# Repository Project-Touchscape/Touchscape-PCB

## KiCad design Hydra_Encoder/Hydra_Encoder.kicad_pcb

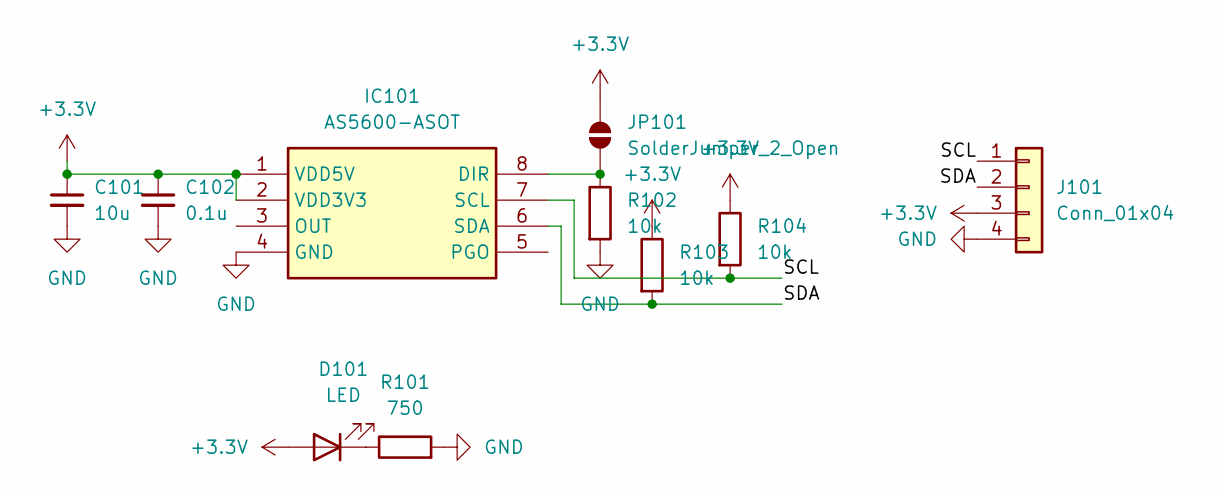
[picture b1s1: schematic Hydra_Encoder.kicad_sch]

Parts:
C101: 10u; C_0805_2012Metric
C102: 0.1u; C_0402_1005Metric
D101: LED; LED_0603_1608Metric
IC101: AS5600-ASOT; SOIC-8_3.9x4.9mm_P1.27mm; Manufacturer_Part_Number AS5600-ASOT; Mouser Part Number 985-AS5600-ASOT
J101: Conn_01x04; CONN_CCSH-W10R-04TR-BK-A_ADA
JP101: SolderJumper_2_Open; SolderJumper-2_P1.3mm_Open_RoundedPad1.0x1.5mm
R101: 750; R_0402_1005Metric
R102, R103, R104: 10k; R_0402_1005Metric

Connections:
+3.3V: C101.1, C102.1, D101.2 (A), IC101.1 (VDD5V), IC101.2 (VDD3V3), J101.3, JP101.2 (B), R103.1, R104.1
/SCL: IC101.7 (SCL), J101.1, R104.2
/SDA: IC101.6 (SDA), J101.2, R103.2
GND: C101.2, C102.2, IC101.4 (GND), J101.4, R101.2, R102.2
unnamed: D101.1 (K), R101.1
unnamed: IC101.8 (DIR), JP101.1 (A), R102.1

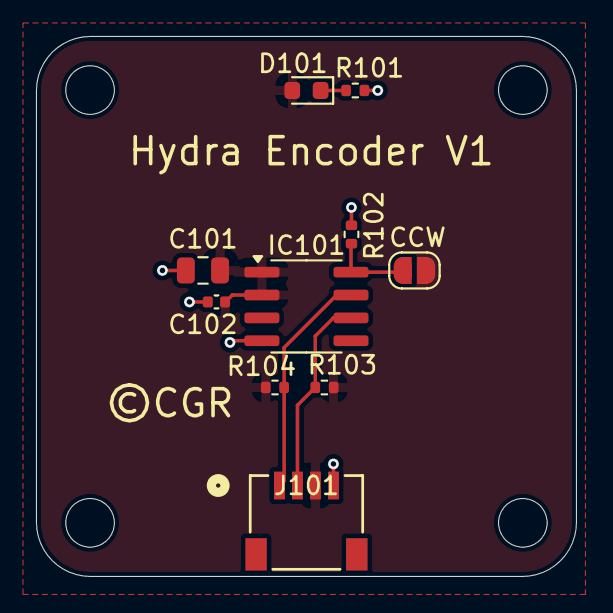
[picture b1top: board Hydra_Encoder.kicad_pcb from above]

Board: 2 copper layers, 30.0 x 30.0 mm, 10 parts (0 on the bottom side), 6 nets.

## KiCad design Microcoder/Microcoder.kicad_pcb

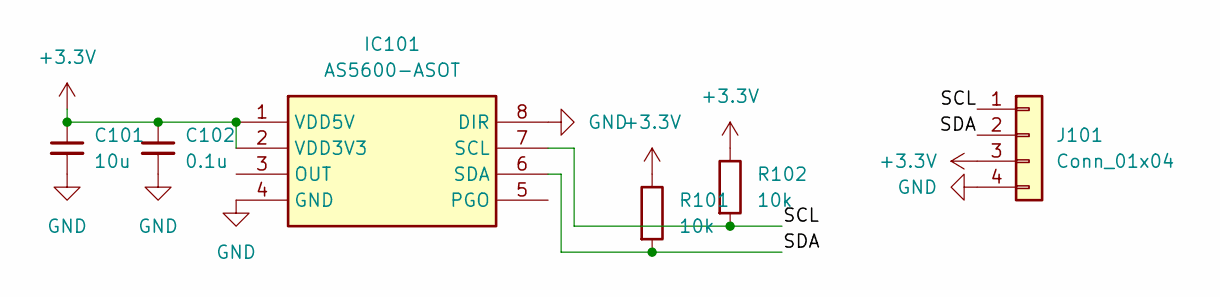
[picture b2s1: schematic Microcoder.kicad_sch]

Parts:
C101: 10u; C_0805_2012Metric
C102: 0.1u; C_0402_1005Metric
IC101: AS5600-ASOT; SOIC-8_3.9x4.9mm_P1.27mm; Manufacturer_Part_Number AS5600-ASOT; Mouser Part Number 985-AS5600-ASOT
J101: Conn_01x04; CONN_CCSH-W10R-04TR-BK-A_ADA
R101, R102: 10k; R_0402_1005Metric

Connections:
+3.3V: C101.1, C102.1, IC101.1 (VDD5V), IC101.2 (VDD3V3), J101.3, R101.1, R102.1
/SCL: IC101.7 (SCL), J101.1, R102.2
/SDA: IC101.6 (SDA), J101.2, R101.2
GND: C101.2, C102.2, IC101.4 (GND), IC101.8 (DIR), J101.4

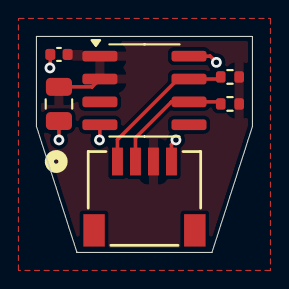
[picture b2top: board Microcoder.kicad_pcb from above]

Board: 2 copper layers, 12.0 x 12.0 mm, 6 parts (0 on the bottom side), 4 nets.

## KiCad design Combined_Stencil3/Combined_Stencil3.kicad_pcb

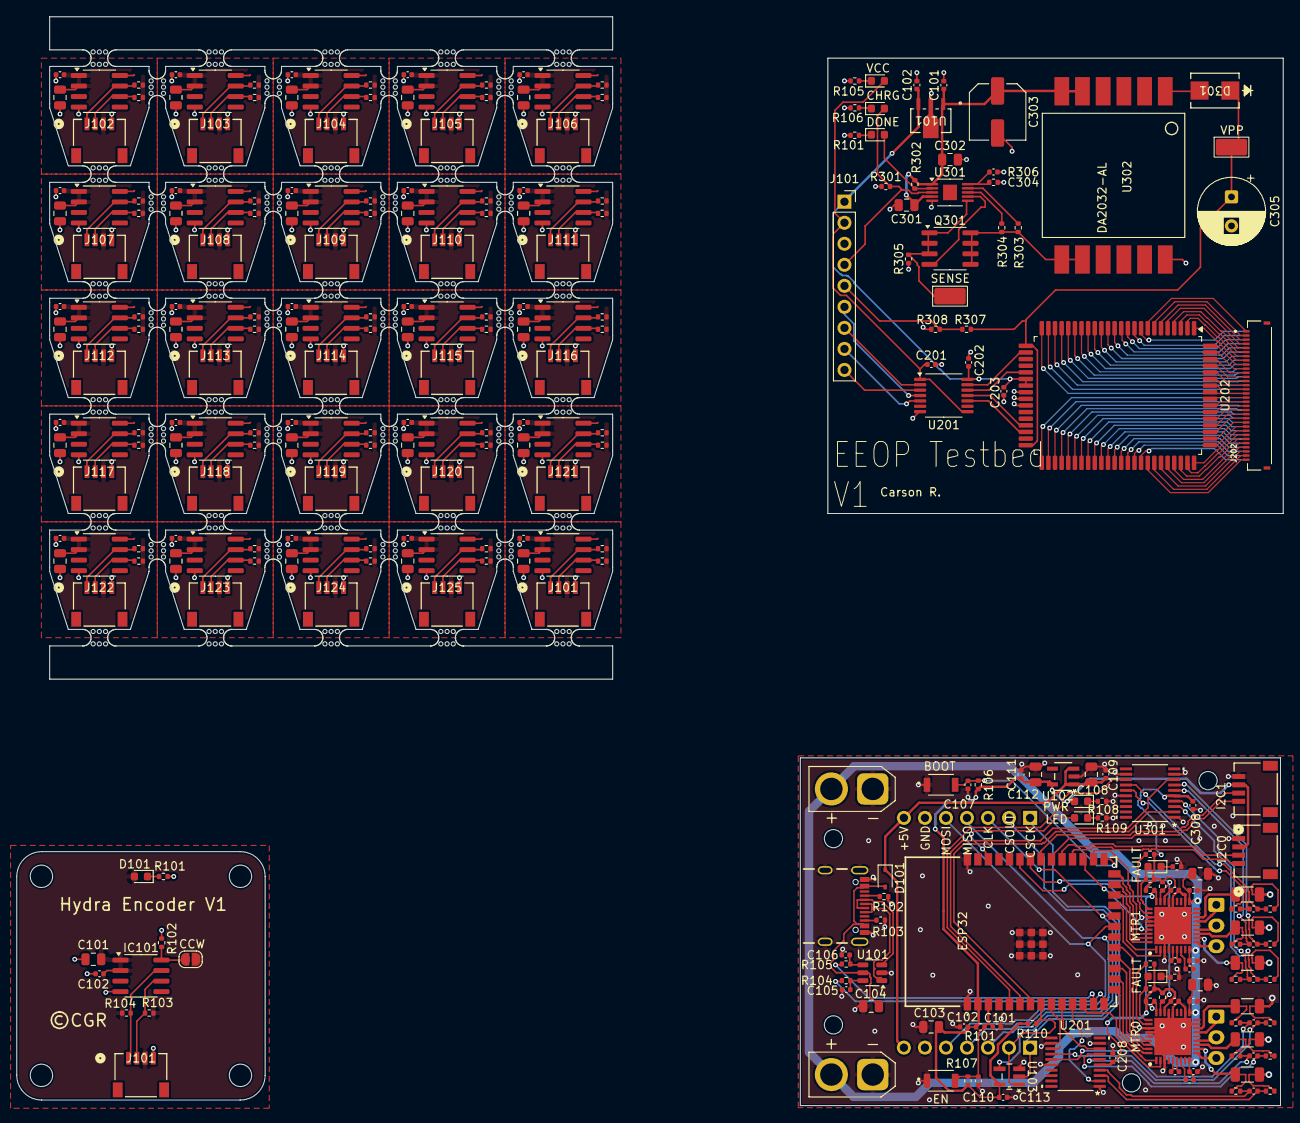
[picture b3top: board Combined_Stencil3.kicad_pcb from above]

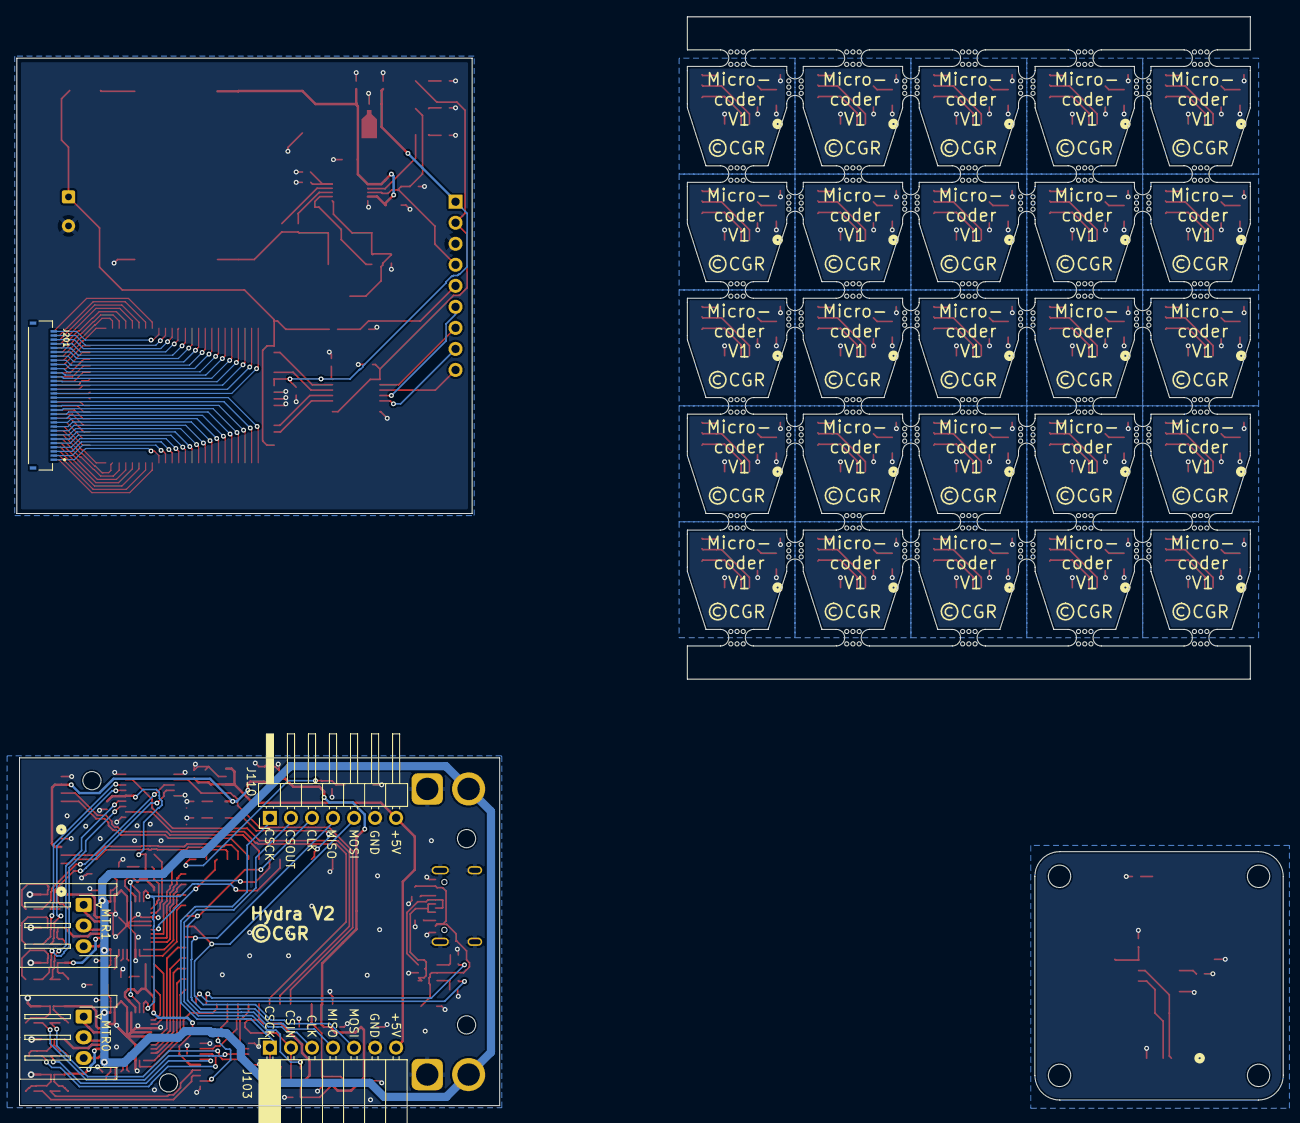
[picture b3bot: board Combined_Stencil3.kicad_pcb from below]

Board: 2 copper layers, 153.0 x 131.5 mm, 341 parts (5 on the bottom side), 174 nets.

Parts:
C101, C101#2, C103, C103#2, C104, C105#2, C107, C108, C109#2, C111#2, C112, C113, C115, C117, C119, C121, C123, C125, C127, C129, C131, C133, C135, C137, C139, C141, C143, C145, C147, C149, C206, C301, C302#2, C306: 10u; C_0805_2012Metric
C101#3, C101#4, C102, C102#2, C102#3, C102#4, C104#2, C106, C107#2, C108#2, C109, C110, C110#2, C111, C112#2, C113#2, C114, C116, C118, C120, C122, C124, C126, C128, C130, C132, C134, C136, C138, C140, C142, C144, C146, C148, C150, C201#2, C202, C202#2, C203#2, C207, C208, C209, C302, C307, C308, C309: 0.1u; C_0402_1005Metric
C105, C106#2, C304#2: 20p; C_0402_1005Metric
C201, C301#2: 0.01u; C_0402_1005Metric
C203, C204, C205, C303, C304, C305: 22n; C_0402_1005Metric
C210, C310: 0.47u; C_0402_1005Metric
C303#2: 56u; C_Elec_6.3x5.8
C305#2: 4.7u; CP_Radial_D8.0mm_P3.50mm
D101, D101#3, D102, D102#2, D103, D103#2, D201, D301#2: LED; LED_0603_1608Metric
D101#2: BAT60A; D_SOD-323
D301: D; SMB_DIO
IC101, IC101#3, IC102, IC103, IC104, IC105, IC106, IC107, IC108, IC109, IC110, IC111, IC112, IC113, IC114, IC115, IC116, IC117, IC118, IC119, IC120, IC121, IC122, IC123, IC124, IC125: AS5600-ASOT; SOIC-8_3.9x4.9mm_P1.27mm
IC101#2: ESP32-S3-WROOM-1-N4; ESP32S3WROOM1N4
IC201, IC301: DRV8313RHHR; QFN50P600X600X100-37N-D
J101, J101#2, J102#2, J103, J104, J104#2, J105, J106, J107, J107#2, J108, J109#2, J110, J111, J112, J113, J114, J115, J116, J117, J118, J119, J120, J121, J122, J123, J124, J125: Conn_01x04; CONN_CCSH-W10R-04TR-BK-A_ADA
J101#3: Conn_01x09; PinSocket_1x09_P2.54mm_Vertical
J101#4: USB4105-GF-A; GCT_USB4105-GF-A
J102, J109: Conn_01x02; AMASS_XT30U-F_1x02_P5.0mm_Vertical
J103#2: Conn_01x07; PinSocket_1x07_P2.54mm_Horizontal
J105#2, J108#2: Conn_01x03; JST_XH_S3B-XH-A-1_1x03_P2.50mm_Horizontal
J110#2: Conn_01x07; PinHeader_1x07_P2.54mm_Horizontal
J201, J202: Conn_01x32; HRS_FH34SRJ-32S-0.5SH_50_
JP101: SolderJumper_2_Open; SolderJumper-2_P1.3mm_Open_RoundedPad1.0x1.5mm
Q301: MCQ15N10YA; SOIC-8_3.9x4.9mm_P1.27mm
R101, R101#4, R102#2, R102#3, R103#2, R104, R104#3, R105, R106, R107, R107#2, R108, R110, R110#2, R111, R113, R114, R116, R117, R119, R120, R122, R123, R125, R126, R128, R129, R131, R132, R134, R135, R137, R138, R140, R141, R143, R144, R146, R147, R149, R150, R152, R153, R155, R156, R158, R159, R161, R162, R164, R165, R167, R168, R170, R171, R173, R174, R207, R208, R209, R210, R301, R307, R308, R309, R310: 10k; R_0402_1005Metric
R101#2: 750; R_0402_1005Metric
R101#3, R105#2, R106#2, R108#2, R109, R211, R311: 500; R_0402_1005Metric
R102, R103: 5.1kΩ; R_0402_1005Metric
R104#2, R105#3: 22Ω; R_0402_1005Metric
R201, R202, R203, R204, R205, R206, R301#2, R302#2, R303, R304#2, R305#2, R306: 10; R_0402_1005Metric
R212, R213, R214, R312, R313, R314: 25m; R_1206_3216Metric
R302: 100k; R_0402_1005Metric
R303#2: 60.4k; R_0402_1005Metric
R304: 43k; R_0402_1005Metric
R305: 13; R_0402_1005Metric
R306#2: 2.49k; R_0402_1005Metric
R307#2: 30M; R_0402_1005Metric
R308#2: 300k; R_0402_1005Metric
SW101, SW102: SW_SPST; SW_B3U-1000P
TP101, TP302: TestPoint; TestPoint_Keystone_5019_Miniature
U101: AS78L05RTR-E1; SOT-89_3MC_MCH
U101#2: USBLC6-2SC6; SOT-23-6
U102: MIC5504-3.3YM5-TR; SOT-23-5_MC_MCH
U103: SN74LVC1G80DBVR; DBV5
U201: TXB0104PW; TSSOP-14_4.4x5mm_P0.65mm
U201#2, U301: INA4181A3IPWR; PW20_TEX
U202: HV507PG-G; PQFP-80_14x20mm_P0.8mm
U301#2: LT3750AEMS-TRPBF; MSOP-10-1EP_3x3mm_P0.5mm_EP1.68x1.88mm
U302: DA2032-AL
mouse-bite-2mm-slot, mouse-bite-2mm-slot1, mouse-bite-2mm-slot3, mouse-bite-2mm-slot4, mouse-bite-2mm-slot5, mouse-bite-2mm-slot6, mouse-bite-2mm-slot7, mouse-bite-2mm-slot8, mouse-bite-2mm-slot9, mouse-bite-2mm-slot10, mouse-bite-2mm-slot11, mouse-bite-2mm-slot13, mouse-bite-2mm-slot14, mouse-bite-2mm-slot15, mouse-bite-2mm-slot16, mouse-bite-2mm-slot17, mouse-bite-2mm-slot18, mouse-bite-2mm-slot19, mouse-bite-2mm-slot20, mouse-bite-2mm-slot21, mouse-bite-2mm-slot23, mouse-bite-2mm-slot24, mouse-bite-2mm-slot25, mouse-bite-2mm-slot26, mouse-bite-2mm-slot27, mouse-bite-2mm-slot28, mouse-bite-2mm-slot29, mouse-bite-2mm-slot30, mouse-bite-2mm-slot31, mouse-bite-2mm-slot33, mouse-bite-2mm-slot34, mouse-bite-2mm-slot35, mouse-bite-2mm-slot36, mouse-bite-2mm-slot37, mouse-bite-2mm-slot38, mouse-bite-2mm-slot39, mouse-bite-2mm-slot40, mouse-bite-2mm-slot41, mouse-bite-2mm-slot41#2, mouse-bite-2mm-slot43, mouse-bite-2mm-slot43#2, mouse-bite-2mm-slot44, mouse-bite-2mm-slot45, mouse-bite-2mm-slot45#2, mouse-bite-2mm-slot46, mouse-bite-2mm-slot47, mouse-bite-2mm-slot47#2, mouse-bite-2mm-slot48, mouse-bite-2mm-slot#2, mouse-bite-2mm-slot#3: VAL**; mouse-bite-2mm-slot

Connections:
+3.3V: C101.1, C101#2.1, C102.2, C102#3.1, C102#4.1, C103.2, C103#2.1, C104#2.1, C105#2.1, C106.1, C107.1, C108#2.1, C109#2.1, C110#2.1, C111.1, C111#2.1, C112.1, C112#2.1, C113.1, C113#2.1, C114.1, C115.1, C116.1, C117.1, C118.1, C119.1, C120.1, C121.1, C122.1, C123.1, C124.1, C125.1, C126.1, C127.1, C128.1, C129.1, C130.1, C131.1, C132.1, C133.1, C134.1, C135.1, C136.1, C137.1, C138.1, C139.1, C140.1, C141.1, C142.1, C143.1, C144.1, C145.1, C146.1, C147.1, C148.1, C149.1, C150.1, C201#2.2, D101.2 (A), D101#3.2 (A), D102.2 (A), IC101.1 (VDD5V), IC101.2 (VDD3V3), IC101#2.2 (3V3), IC101#3.1 (VDD5V), IC101#3.2 (VDD3V3), IC102.1 (VDD5V), IC102.2 (VDD3V3), IC103.1 (VDD5V), IC103.2 (VDD3V3), IC104.1 (VDD5V), IC104.2 (VDD3V3), IC105.1 (VDD5V), IC105.2 (VDD3V3), IC106.1 (VDD5V), IC106.2 (VDD3V3), IC107.1 (VDD5V), IC107.2 (VDD3V3), IC108.1 (VDD5V), IC108.2 (VDD3V3), IC109.1 (VDD5V), IC109.2 (VDD3V3), IC110.1 (VDD5V), IC110.2 (VDD3V3), IC111.1 (VDD5V), IC111.2 (VDD3V3), IC112.1 (VDD5V), IC112.2 (VDD3V3), IC113.1 (VDD5V), IC113.2 (VDD3V3), IC114.1 (VDD5V), IC114.2 (VDD3V3), IC115.1 (VDD5V), IC115.2 (VDD3V3), IC116.1 (VDD5V), IC116.2 (VDD3V3), IC117.1 (VDD5V), IC117.2 (VDD3V3), IC118.1 (VDD5V), IC118.2 (VDD3V3), IC119.1 (VDD5V), IC119.2 (VDD3V3), IC120.1 (VDD5V), IC120.2 (VDD3V3), IC121.1 (VDD5V), IC121.2 (VDD3V3), IC122.1 (VDD5V), IC122.2 (VDD3V3), IC123.1 (VDD5V), IC123.2 (VDD3V3), IC124.1 (VDD5V), IC124.2 (VDD3V3), IC125.1 (VDD5V), IC125.2 (VDD3V3), J101.3, J101#2.3, J101#3.2, J102#2.3, J103.3, J104.3, J104#2.3, J105.3, J106.3, J107.3, J107#2.3, J108.3, J109#2.3, J110.3, J111.3, J112.3, J113.3, J114.3, J115.3, J116.3, J117.3, J118.3, J119.3, J120.3, J121.3, J122.3, J123.3, J124.3, J125.3, JP101.2 (B), R101.1, R101#4.1, R102#2.1, R103#2.1, R104.1, R104#3.1, R105.1, R106.1, R107.1, R107#2.1, R108.1, R110.1, R110#2.1, R111.1, R113.1, R114.1, R116.1, R117.1, R119.1, R120.1, R122.1, R123.1, R125.1, R126.1, R128.1, R129.1, R131.1, R132.1, R134.1, R135.1, R137.1, R138.1, R140.1, R141.1, R143.1, R144.1, R146.1, R147.1, R149.1, R150.1, R152.1, R153.1, R155.1, R156.1, R158.1, R159.1, R161.1, R162.1, R164.1, R165.1, R167.1, R168.1, R170.1, R171.1, R173.1, R174.1, U102.5 (VOUT), U103.5 (VCC), U201.1 (VCCA), U201.8 (OE)
+5V: C101#3.1, C108.1, C109.1, C301.1, C302#2.1, C303#2.1, D101#2.1 (K), J103#2.7, J110#2.7, R302.1, U101.1 (OUTPUT), U102.1 (VIN), U102.3 (EN), U301#2.1 (VTRANS), U301#2.4 (VCC), U302.P$5, U302.P$6
/CHARGE: D102#2.2 (A), J101#3.4, R301.2, U301#2.3 (CHARGE)
/CHIP_PU: C101#4.1, C110.1, IC101#2.3 (EN), R101#4.2, R107#2.2, SW102.2 (B)
/CLK: IC101#2.22 (IO14), J103#2.3, J110#2.3
/CSCK: J103#2.1, J110#2.1, U103.2 (CLK)
/CSIN: IC101#2.8 (IO15), J103#2.2, R110.2, U103.1 (D)
/CSOUT: J110#2.2, U103.4 (*Q)
/D+: IC101#2.14 (IO20), R104#2.1
/D-: IC101#2.13 (IO19), R105#3.1
/DONE: D103.2 (A), R302.2, U301#2.2 (DONE)
/Driver_Unit1/FAULT: D301#2.2 (A), IC301.28 (NFAULT), R308.1
/Driver_Unit1/IN+1: C303.2, R301#2.1, U301.4 (IN+1)
/Driver_Unit1/IN+2: C304.2, R303.1, U301.6 (IN+2)
/Driver_Unit1/IN+3: C305.2, R305#2.1, U301.15 (IN+3)
/Driver_Unit1/IN-1: C303.1, R302#2.1, U301.3 (IN-1)
/Driver_Unit1/IN-2: C304.1, R304#2.1, U301.7 (IN-2)
/Driver_Unit1/IN-3: C305.1, R306.1, U301.14 (IN-3)
/Driver_Unit1/L3V3: C308.2, C310.2, IC301.25 (V3P3), R307.2, R308.2, R309.2, R310.2, U301.5 (VS)
/Driver_Unit1/SGND1: IC301.11 (PGND1), R301#2.2, R312.1
/Driver_Unit1/SGND2: IC301.12 (PGND2), R303.2, R313.1
/Driver_Unit1/SGND3: IC301.16 (PGND3), R305#2.2, R314.1
/Driver_Unit/FAULT: D201.2 (A), IC201.28 (NFAULT), R208.1
/Driver_Unit/IN+1: C203.2, R201.1, U201#2.4 (IN+1)
/Driver_Unit/IN+2: C204.2, R203.1, U201#2.6 (IN+2)
/Driver_Unit/IN+3: C205.2, R205.1, U201#2.15 (IN+3)
/Driver_Unit/IN-1: C203.1, R202.1, U201#2.3 (IN-1)
/Driver_Unit/IN-2: C204.1, R204.1, U201#2.7 (IN-2)
/Driver_Unit/IN-3: C205.1, R206.1, U201#2.14 (IN-3)
/Driver_Unit/L3V3: C208.2, C210.2, IC201.25 (V3P3), R207.2, R208.2, R209.2, R210.2, U201#2.5 (VS)
/Driver_Unit/SGND1: IC201.11 (PGND1), R201.2, R212.1
/Driver_Unit/SGND2: IC201.12 (PGND2), R203.2, R213.1
/Driver_Unit/SGND3: IC201.16 (PGND3), R205.2, R214.1
/EEOP_Driver/BL: J101#3.9, U201.3 (A2)
/EEOP_Driver/BLout: U201.12 (B2), U202.29 (*BL)
/EEOP_Driver/CLK: J101#3.6, U201.4 (A3)
/EEOP_Driver/CLKout: U201.11 (B3), U202.37 (CLK)
/EEOP_Driver/DIN: J101#3.7, U201.2 (A1)
/EEOP_Driver/DINout: U201.13 (B1), U202.26 (DIOA)
/EEOP_Driver/LE: J101#3.8, U201.5 (A4)
/EEOP_Driver/LEout: U201.10 (B4), U202.38 (*LE)
/EEOP_Driver/OUT1: J201.16, U202.41 (HVOUT1)
/EEOP_Driver/OUT2: J201.15, U202.42 (HVOUT2)
/EEOP_Driver/OUT3: J201.14, U202.43 (HVOUT3)
/EEOP_Driver/OUT4: J201.13, U202.44 (HVOUT4)
/EEOP_Driver/OUT5: J201.12, U202.45 (HVOUT5)
/EEOP_Driver/OUT6: J201.11, U202.46 (HVOUT6)
/EEOP_Driver/OUT7: J201.10, U202.47 (HVOUT7)
/EEOP_Driver/OUT8: J201.9, U202.48 (HVOUT8)
/EEOP_Driver/OUT9: J201.8, U202.49 (HVOUT9)
/EEOP_Driver/OUT10: J201.7, U202.50 (HVOUT10)
/EEOP_Driver/OUT11: J201.6, U202.51 (HVOUT11)
/EEOP_Driver/OUT12: J201.5, U202.52 (HVOUT12)
/EEOP_Driver/OUT13: J201.4, U202.53 (HVOUT13)
/EEOP_Driver/OUT14: J201.3, U202.54 (HVOUT14)
/EEOP_Driver/OUT15: J201.2, U202.55 (HVOUT15)
/EEOP_Driver/OUT16: J201.1, U202.56 (HVOUT16)
/EEOP_Driver/OUT17: J202.32, U202.57 (HVOUT17)
/EEOP_Driver/OUT18: J202.31, U202.58 (HVOUT18)
/EEOP_Driver/OUT19: J202.30, U202.59 (HVOUT19)
/EEOP_Driver/OUT20: J202.29, U202.60 (HVOUT20)
/EEOP_Driver/OUT21: J202.28, U202.61 (HVOUT21)
/EEOP_Driver/OUT22: J202.27, U202.62 (HVOUT22)
/EEOP_Driver/OUT23: J202.26, U202.63 (HVOUT23)
/EEOP_Driver/OUT24: J202.25, U202.64 (HVOUT24)
/EEOP_Driver/OUT25: J202.24, U202.65 (HVOUT25)
/EEOP_Driver/OUT26: J202.23, U202.66 (HVOUT26)
/EEOP_Driver/OUT27: J202.22, U202.67 (HVOUT27)
/EEOP_Driver/OUT28: J202.21, U202.68 (HVOUT28)
/EEOP_Driver/OUT29: J202.20, U202.69 (HVOUT29)
/EEOP_Driver/OUT30: J202.19, U202.70 (HVOUT30)
/EEOP_Driver/OUT31: J202.18, U202.71 (HVOUT31)
/EEOP_Driver/OUT32: J202.17, U202.72 (HVOUT32)
/EEOP_Driver/OUT33: J202.16, U202.73 (HVOUT33)
/EEOP_Driver/OUT34: J202.15, U202.74 (HVOUT34)
/EEOP_Driver/OUT35: J202.14, U202.75 (HVOUT35)
/EEOP_Driver/OUT36: J202.13, U202.76 (HVOUT36)
/EEOP_Driver/OUT37: J202.12, U202.77 (HVOUT37)
/EEOP_Driver/OUT38: J202.11, U202.78 (HVOUT38)
/EEOP_Driver/OUT39: J202.10, U202.79 (HVOUT39)
/EEOP_Driver/OUT40: J202.9, U202.80 (HVOUT40)
/EEOP_Driver/OUT41: J202.8, U202.1 (HVOUT41)
/EEOP_Driver/OUT42: J202.7, U202.2 (HVOUT42)
/EEOP_Driver/OUT43: J202.6, U202.3 (HVOUT43)
/EEOP_Driver/OUT44: J202.5, U202.4 (HVOUT44)
/EEOP_Driver/OUT45: J202.4, U202.5 (HVOUT45)
/EEOP_Driver/OUT46: J202.3, U202.6 (HVOUT46)
/EEOP_Driver/OUT47: J202.2, U202.7 (HVOUT47)
/EEOP_Driver/OUT48: J202.1, U202.8 (HVOUT48)
/EEOP_Driver/OUT49: J201.32, U202.9 (HVOUT49)
/EEOP_Driver/OUT50: J201.31, U202.10 (HVOUT50)
/EEOP_Driver/OUT51: J201.30, U202.11 (HVOUT51)
/EEOP_Driver/OUT52: J201.29, U202.12 (HVOUT52)
/EEOP_Driver/OUT53: J201.28, U202.13 (HVOUT53)
/EEOP_Driver/OUT54: J201.27, U202.14 (HVOUT54)
/EEOP_Driver/OUT55: J201.26, U202.15 (HVOUT55)
/EEOP_Driver/OUT56: J201.25, U202.16 (HVOUT56)
/EEOP_Driver/OUT57: J201.24, U202.17 (HVOUT57)
/EEOP_Driver/OUT58: J201.23, U202.18 (HVOUT58)
/EEOP_Driver/OUT59: J201.22, U202.19 (HVOUT59)
/EEOP_Driver/OUT60: J201.21, U202.20 (HVOUT60)
/EEOP_Driver/OUT61: J201.20, U202.21 (HVOUT61)
/EEOP_Driver/OUT62: J201.19, U202.22 (HVOUT62)
/EEOP_Driver/OUT63: J201.18, U202.23 (HVOUT63)
/EEOP_Driver/OUT64: J201.17, U202.24 (HVOUT64)
/EN1A: IC101#2.15 (IO3), IC201.1 (EN1)
/EN1B: IC101#2.24 (IO47), IC301.1 (EN1)
/EN2A: IC101#2.17 (IO9), IC201.35 (EN2)
/EN2B: IC101#2.26 (IO45), IC301.35 (EN2)
/EN3A: IC101#2.19 (IO11), IC201.33 (EN3)
/EN3B: IC101#2.29 (IO36), IC301.33 (EN3)
/GPIO0: C107#2.1, IC101#2.27 (IO0), R106.2, SW101.2 (B)
/IN1A: IC101#2.12 (IO8), IC201.2 (IN1)
/IN1B: IC101#2.23 (IO21), IC301.2 (IN1)
/IN2A: IC101#2.16 (IO46), IC201.36 (IN2)
/IN2B: IC101#2.25 (IO48), IC301.36 (IN2)
/IN3A: IC101#2.18 (IO10), IC201.34 (IN3)
/IN3B: IC101#2.28 (IO35), IC301.34 (IN3)
/LED: D103#2.2 (A), IC101#2.38 (IO2)
/MISO: IC101#2.20 (IO12), J103#2.4, J110#2.4
/MOSI: IC101#2.21 (IO13), J103#2.5, J110#2.5
/OUT1A: IC201.10 (OUT1), J105#2.3
/OUT1B: IC301.10 (OUT1), J108#2.3
/OUT2A: IC201.13 (OUT2), J105#2.2
/OUT2B: IC301.13 (OUT2), J108#2.2
/OUT3A: IC201.15 (OUT3), J105#2.1
/OUT3B: IC301.15 (OUT3), J108#2.1
/RESET: IC101#2.34 (IO41), IC201.26 (NRESET), IC301.26 (NRESET), R210.1, R310.1
/SCL: IC101.7 (SCL), IC101#3.7 (SCL), IC102.7 (SCL), IC103.7 (SCL), IC104.7 (SCL), IC105.7 (SCL), IC106.7 (SCL), IC107.7 (SCL), IC108.7 (SCL), IC109.7 (SCL), IC110.7 (SCL), IC111.7 (SCL), IC112.7 (SCL), IC113.7 (SCL), IC114.7 (SCL), IC115.7 (SCL), IC116.7 (SCL), IC117.7 (SCL), IC118.7 (SCL), IC119.7 (SCL), IC120.7 (SCL), IC121.7 (SCL), IC122.7 (SCL), IC123.7 (SCL), IC124.7 (SCL), IC125.7 (SCL), J101.1, J101#2.1, J102#2.1, J103.1, J104.1, J105.1, J106.1, J107.1, J108.1, J109#2.1, J110.1, J111.1, J112.1, J113.1, J114.1, J115.1, J116.1, J117.1, J118.1, J119.1, J120.1, J121.1, J122.1, J123.1, J124.1, J125.1, R102#2.2, R104#3.2, R105.2, R108.2, R111.2, R114.2, R117.2, R120.2, R123.2, R126.2, R129.2, R132.2, R135.2, R138.2, R141.2, R144.2, R147.2, R150.2, R153.2, R156.2, R159.2, R162.2, R165.2, R168.2, R171.2, R174.2
/SCL1: IC101#2.30 (IO37), J107#2.1
/SCL2: IC101#2.32 (IO39), J104#2.1
/SDA: IC101.6 (SDA), IC101#3.6 (SDA), IC102.6 (SDA), IC103.6 (SDA), IC104.6 (SDA), IC105.6 (SDA), IC106.6 (SDA), IC107.6 (SDA), IC108.6 (SDA), IC109.6 (SDA), IC110.6 (SDA), IC111.6 (SDA), IC112.6 (SDA), IC113.6 (SDA), IC114.6 (SDA), IC115.6 (SDA), IC116.6 (SDA), IC117.6 (SDA), IC118.6 (SDA), IC119.6 (SDA), IC120.6 (SDA), IC121.6 (SDA), IC122.6 (SDA), IC123.6 (SDA), IC124.6 (SDA), IC125.6 (SDA), J101.2, J101#2.2, J102#2.2, J103.2, J104.2, J105.2, J106.2, J107.2, J108.2, J109#2.2, J110.2, J111.2, J112.2, J113.2, J114.2, J115.2, J116.2, J117.2, J118.2, J119.2, J120.2, J121.2, J122.2, J123.2, J124.2, J125.2, R101.2, R103#2.2, R104.2, R107.2, R110#2.2, R113.2, R116.2, R119.2, R122.2, R125.2, R128.2, R131.2, R134.2, R137.2, R140.2, R143.2, R146.2, R149.2, R152.2, R155.2, R158.2, R161.2, R164.2, R167.2, R170.2, R173.2
/SDA1: IC101#2.31 (IO38), J107#2.2
/SDA2: IC101#2.33 (IO40), J104#2.2
/SENSE1A: IC101#2.11 (IO18), U201#2.2 (OUT1)
/SENSE1B: IC101#2.7 (IO7), U301.2 (OUT1)
/SENSE2A: IC101#2.10 (IO17), U201#2.8 (OUT2)
/SENSE2B: IC101#2.6 (IO6), U301.8 (OUT2)
/SENSE3A: IC101#2.9 (IO16), U201#2.13 (OUT3)
/SENSE3B: IC101#2.5 (IO5), U301.13 (OUT3)
/SLEEP: IC101#2.35 (IO42), IC201.27 (NSLEEP), IC301.27 (NSLEEP), R209.1, R309.1
/VREF: J101#3.5, R307#2.1, R308#2.2
GND: C101.2, C101#2.2, C101#3.2, C101#4.2, C102.1, C102#2.2, C102#3.2, C102#4.2, C103.1, C103#2.2, C104.1, C104#2.2, C105.2, C105#2.2, C106.2, C106#2.2, C107.2, C107#2.2, C108.2, C108#2.2, C109.2, C109#2.2, C110.2, C110#2.2, C111.2, C111#2.2, C112.2, C112#2.2, C113.2, C113#2.2, C114.2, C115.2, C116.2, C117.2, C118.2, C119.2, C120.2, C121.2, C122.2, C123.2, C124.2, C125.2, C126.2, C127.2, C128.2, C129.2, C130.2, C131.2, C132.2, C133.2, C134.2, C135.2, C136.2, C137.2, C138.2, C139.2, C140.2, C141.2, C142.2, C143.2, C144.2, C145.2, C146.2, C147.2, C148.2, C149.2, C150.2, C201#2.1, C202#2.2, C203#2.2, C206.1, C207.1, C208.1, C209.1, C210.1, C301.2, C302#2.2, C303#2.2, C304#2.1, C305#2.2, C306.1, C307.1, C308.1, C309.1, C310.1, IC101.4 (GND), IC101#2.1 (GND_1), IC101#2.40 (GND_2), IC101#2.41 (GND_3), IC101#2.42 (GND_4), IC101#2.43 (GND_5), IC101#2.44 (GND_6), IC101#2.45 (GND_7), IC101#2.46 (GND_8), IC101#2.47 (GND_9), IC101#2.48 (GND_10), IC101#2.49 (GND_11), IC101#3.4 (GND), IC102.4 (GND), IC103.4 (GND), IC104.4 (GND), IC105.4 (GND), IC106.4 (GND), IC107.4 (GND), IC108.4 (GND), IC109.4 (GND), IC110.4 (GND), IC111.4 (GND), IC112.4 (GND), IC113.4 (GND), IC114.4 (GND), IC115.4 (GND), IC116.4 (GND), IC117.4 (GND), IC118.4 (GND), IC119.4 (GND), IC120.4 (GND), IC121.4 (GND), IC122.4 (GND), IC123.4 (GND), IC124.4 (GND), IC125.4 (GND), IC201.3 (GND_1), IC201.17 (GND_2), IC201.20 (GND_3), IC201.23 (GND_4), IC201.24 (GND_5), IC201.30 (GND_6), IC201.31 (GND_7), IC201.32 (GND_8), IC201.37 (EP), IC301.3 (GND_1), IC301.17 (GND_2), IC301.20 (GND_3), IC301.23 (GND_4), IC301.24 (GND_5), IC301.30 (GND_6), IC301.31 (GND_7), IC301.32 (GND_8), IC301.37 (EP), J101.4, J101#2.4, J101#3.3, J101#4.A1_B12 (GND), J101#4.B1_A12 (GND__1), J101#4.SH1 (SHELL_GND), J101#4.SH2 (SHELL_GND__1), J101#4.SH3 (SHELL_GND__2), J101#4.SH4 (SHELL_GND__3), J102.1, J102#2.4, J103.4, J103#2.6, J104.4, J104#2.4, J105.4, J106.4, J107.4, J107#2.4, J108.4, J109.1, J109#2.4, J110.4, J110#2.6, J111.4, J112.4, J113.4, J114.4, J115.4, J116.4, J117.4, J118.4, J119.4, J120.4, J121.4, J122.4, J123.4, J124.4, J125.4, R101#2.2, R101#3.2, R102.2, R102#3.2, R103.2, R105#2.2, R106#2.2, R108#2.2, R109.2, R202.2, R204.2, R206.2, R211.2, R212.2, R213.2, R214.2, R301.1, R302#2.2, R304#2.2, R305.1, R306.2, R306#2.2, R308#2.1, R311.2, R312.2, R313.2, R314.2, SW101.1 (A), SW102.1 (A), U101.2 (GND), U101#2.2 (GND), U102.2 (GND), U103.3 (GND), U201.7 (GND), U201#2.1 (REF1), U201#2.9 (REF2), U201#2.12 (REF3), U201#2.16 (GND), U202.32 (DIR), U202.33 (GND), U202.34 (HVGND), U301.1 (REF1), U301.9 (REF2), U301.12 (REF3), U301.16 (GND), U301#2.5 (GND), U302.P$12
unnamed: C105.1, R104#2.2, U101#2.6 (I/O1)
unnamed: C106#2.1, R105#3.2, U101#2.4 (I/O2)
unnamed: C104.2, D101#2.2 (A), J101#4.A4_B9 (VBUS), J101#4.B4_A9 (VBUS__1), U101#2.5 (VBUS)
unnamed: D101.1 (K), D101#3.1 (K), R101#2.1, R105#2.1
unnamed: D102.1 (K), D102#2.1 (K), R106#2.1, R108#2.1
unnamed: D103.1 (K), D103#2.1 (K), R101#3.1, R109.1
unnamed: D201.1 (K), R211.1
unnamed: D301.2 (A), U302.P$1
unnamed: D301#2.1 (K), R311.1
unnamed: IC101.8 (DIR), IC101#3.8 (DIR), IC102.8 (DIR), IC103.8 (DIR), IC104.8 (DIR), IC105.8 (DIR), IC106.8 (DIR), IC107.8 (DIR), IC108.8 (DIR), IC109.8 (DIR), IC110.8 (DIR), IC111.8 (DIR), IC112.8 (DIR), IC113.8 (DIR), IC114.8 (DIR), IC115.8 (DIR), IC116.8 (DIR), IC117.8 (DIR), IC118.8 (DIR), IC119.8 (DIR), IC120.8 (DIR), IC121.8 (DIR), IC122.8 (DIR), IC123.8 (DIR), IC124.8 (DIR), IC125.8 (DIR), JP101.1 (A), R102#3.1
unnamed: C201.1, IC201.6 (CPH)
unnamed: C201.2, IC201.5 (CPL)
unnamed: IC201.29 (NCOMPO), R207.1
unnamed: C202.2, IC201.7 (VCP)
unnamed: C301#2.1, IC301.6 (CPH)
unnamed: C301#2.2, IC301.5 (CPL)
unnamed: IC301.29 (NCOMPO), R307.1
unnamed: C302.2, IC301.7 (VCP)
unnamed: J101#4.A5 (CC1), R102.1
unnamed: J101#4.B5 (CC2), R103.1
unnamed: J101#4.A7 (DN1), J101#4.B7 (DN2), U101#2.3 (I/O2)
unnamed: J101#4.A6 (DP1), J101#4.B6 (DP2), U101#2.1 (I/O1)
unnamed: Q301.5, Q301.6, Q301.7, Q301.8, R303#2.2, R304.2, U302.P$7, U302.P$8
unnamed: Q301.4, U301#2.7 (GATE)
unnamed: C304#2.2, R306#2.1, U301#2.10 (RBG)
unnamed: R304.1, U301#2.8 (RDCM)
unnamed: R303#2.1, U301#2.9 (RVOUT)
unnamed: Q301.1, Q301.2, Q301.3, R305.2, TP302.1, U301#2.6 (SOURCE)
VBUS: C102#2.1, C202#2.1, C203#2.1, J101#3.1, U101.3 (INPUT), U201.14 (VCCB), U202.30 (*POL), U202.31 (VDD)
VMOT: C202.1, C206.2, C207.2, C209.2, C302.1, C306.2, C307.2, C309.2, IC201.9 (VM_1), IC201.19 (VM_2), IC301.9 (VM_1), IC301.19 (VM_2), J102.2, J109.2
VPP: C305#2.1, D301.1 (K), R307#2.2, TP101.1, U202.25 (VPP), U202.40 (VPP)

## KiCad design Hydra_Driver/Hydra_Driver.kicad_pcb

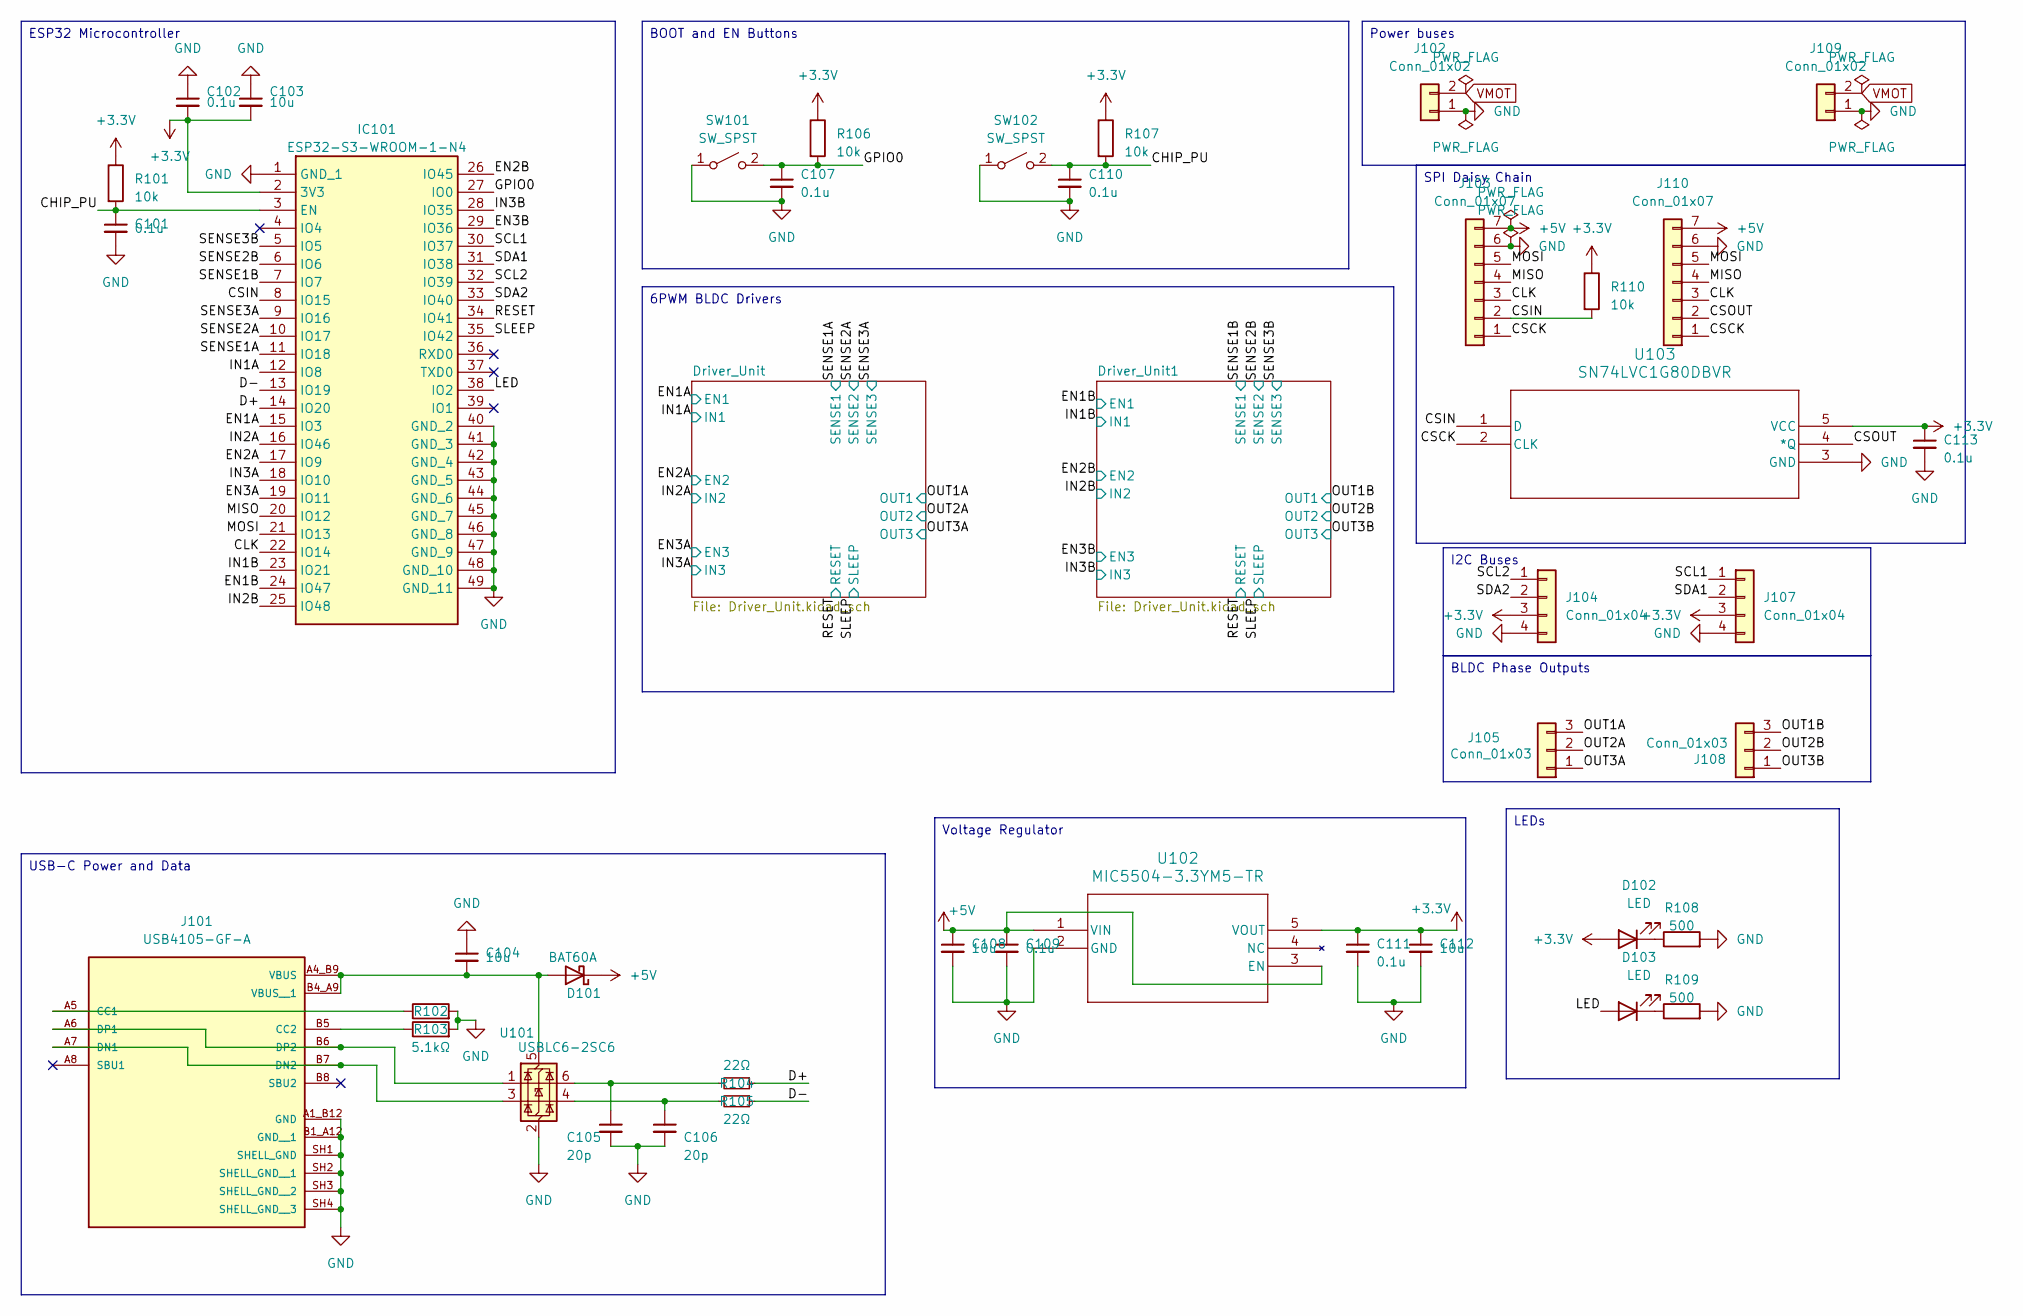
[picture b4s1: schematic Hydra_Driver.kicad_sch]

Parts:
C101, C102, C107, C109, C110, C111, C113: 0.1u; C_0402_1005Metric
C103, C104, C108, C112: 10u; C_0805_2012Metric
C105, C106: 20p; C_0402_1005Metric; LCSC C1648
D101: BAT60A; D_SOD-323; JLCPCB C124187
D102, D103: LED; LED_0603_1608Metric
IC101: ESP32-S3-WROOM-1-N4; ESP32S3WROOM1N4; Manufacturer_Part_Number ESP32-S3-WROOM-1-N4; Mouser Part Number 356-ESP32-S3WROOM1N4
J101: USB4105-GF-A; GCT_USB4105-GF-A; PARTREV B4
J102, J109: Conn_01x02; AMASS_XT30U-F_1x02_P5.0mm_Vertical
J103: Conn_01x07; PinSocket_1x07_P2.54mm_Horizontal
J104, J107: Conn_01x04; CONN_CCSH-W10R-04TR-BK-A_ADA
J105, J108: Conn_01x03; JST_XH_S3B-XH-A-1_1x03_P2.50mm_Horizontal
J110: Conn_01x07; PinHeader_1x07_P2.54mm_Horizontal
R101, R106, R107, R110: 10k; R_0402_1005Metric
R102, R103: 5.1kΩ; R_0402_1005Metric; JLCPCB C23186
R104, R105: 22Ω; R_0402_1005Metric; LCSC C23345
R108, R109: 500; R_0402_1005Metric
SW101, SW102: SW_SPST; SW_B3U-1000P
U101: USBLC6-2SC6; SOT-23-6; JLCPCB C2827654
U102: MIC5504-3.3YM5-TR; SOT-23-5_MC_MCH
U103: SN74LVC1G80DBVR; DBV5

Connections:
+3.3V: C102.2, C103.2, C111.1, C112.1, C113.1, D102.2 (A), IC101.2 (3V3), J104.3, J107.3, R101.1, R106.1, R107.1, R110.1, U102.5 (VOUT), U103.5 (VCC)
+5V: C108.1, C109.1, D101.1 (K), J103.7, J110.7, U102.1 (VIN), U102.3 (EN)
/CHIP_PU: C101.1, C110.1, IC101.3 (EN), R101.2, R107.2, SW102.2 (B)
/CLK: IC101.22 (IO14), J103.3, J110.3
/CSCK: J103.1, J110.1, U103.2 (CLK)
/CSIN: IC101.8 (IO15), J103.2, R110.2, U103.1 (D)
/CSOUT: J110.2, U103.4 (*Q)
/D+: IC101.14 (IO20), R104.1
/D-: IC101.13 (IO19), R105.1
/EN1A: IC101.15 (IO3); also elsewhere on the board
/EN1B: IC101.24 (IO47); also elsewhere on the board
/EN2A: IC101.17 (IO9); also elsewhere on the board
/EN2B: IC101.26 (IO45); also elsewhere on the board
/EN3A: IC101.19 (IO11); also elsewhere on the board
/EN3B: IC101.29 (IO36); also elsewhere on the board
/GPIO0: C107.1, IC101.27 (IO0), R106.2, SW101.2 (B)
/IN1A: IC101.12 (IO8); also elsewhere on the board
/IN1B: IC101.23 (IO21); also elsewhere on the board
/IN2A: IC101.16 (IO46); also elsewhere on the board
/IN2B: IC101.25 (IO48); also elsewhere on the board
/IN3A: IC101.18 (IO10); also elsewhere on the board
/IN3B: IC101.28 (IO35); also elsewhere on the board
/LED: D103.2 (A), IC101.38 (IO2)
/MISO: IC101.20 (IO12), J103.4, J110.4
/MOSI: IC101.21 (IO13), J103.5, J110.5
/OUT1A: J105.3; also elsewhere on the board
/OUT1B: J108.3; also elsewhere on the board
/OUT2A: J105.2; also elsewhere on the board
/OUT2B: J108.2; also elsewhere on the board
/OUT3A: J105.1; also elsewhere on the board
/OUT3B: J108.1; also elsewhere on the board
/RESET: IC101.34 (IO41); also elsewhere on the board
/SCL1: IC101.30 (IO37), J107.1
/SCL2: IC101.32 (IO39), J104.1
/SDA1: IC101.31 (IO38), J107.2
/SDA2: IC101.33 (IO40), J104.2
/SENSE1A: IC101.11 (IO18); also elsewhere on the board
/SENSE1B: IC101.7 (IO7); also elsewhere on the board
/SENSE2A: IC101.10 (IO17); also elsewhere on the board
/SENSE2B: IC101.6 (IO6); also elsewhere on the board
/SENSE3A: IC101.9 (IO16); also elsewhere on the board
/SENSE3B: IC101.5 (IO5); also elsewhere on the board
/SLEEP: IC101.35 (IO42); also elsewhere on the board
GND: C101.2, C102.1, C103.1, C104.1, C105.2, C106.2, C107.2, C108.2, C109.2, C110.2, C111.2, C112.2, C113.2, IC101.1 (GND_1), IC101.40 (GND_2), IC101.41 (GND_3), IC101.42 (GND_4), IC101.43 (GND_5), IC101.44 (GND_6), IC101.45 (GND_7), IC101.46 (GND_8), IC101.47 (GND_9), IC101.48 (GND_10), IC101.49 (GND_11), J101.A1_B12 (GND), J101.B1_A12 (GND__1), J101.SH1 (SHELL_GND), J101.SH2 (SHELL_GND__1), J101.SH3 (SHELL_GND__2), J101.SH4 (SHELL_GND__3), J102.1, J103.6, J104.4, J107.4, J109.1, J110.6, R102.2, R103.2, R108.2, R109.2, SW101.1 (A), SW102.1 (A), U101.2 (GND), U102.2 (GND), U103.3 (GND); also elsewhere on the board
unnamed: C105.1, R104.2, U101.6 (I/O1)
unnamed: C106.1, R105.2, U101.4 (I/O2)
unnamed: C104.2, D101.2 (A), J101.A4_B9 (VBUS), J101.B4_A9 (VBUS__1), U101.5 (VBUS)
unnamed: D102.1 (K), R108.1
unnamed: D103.1 (K), R109.1
unnamed: J101.A5 (CC1), R102.1
unnamed: J101.B5 (CC2), R103.1
unnamed: J101.A7 (DN1), J101.B7 (DN2), U101.3 (I/O2)
unnamed: J101.A6 (DP1), J101.B6 (DP2), U101.1 (I/O1)
VMOT: J102.2, J109.2; also elsewhere on the board

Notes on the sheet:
BLDC Phase Outputs
I2C Buses
LEDs
ESP32 Microcontroller
BOOT and EN Buttons
Voltage Regulator
SPI Daisy Chain
Power buses
6PWM BLDC Drivers
USB-C Power and Data

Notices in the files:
Combined_Stencil3/Combined_Stencil3.kicad_pcb:
©CGR
